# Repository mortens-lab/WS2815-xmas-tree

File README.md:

# WS2815-xmas-tree
Arduino Code and KiCad files for controller

Link to youtube video : https://youtu.be/LrLCPcfc_rA

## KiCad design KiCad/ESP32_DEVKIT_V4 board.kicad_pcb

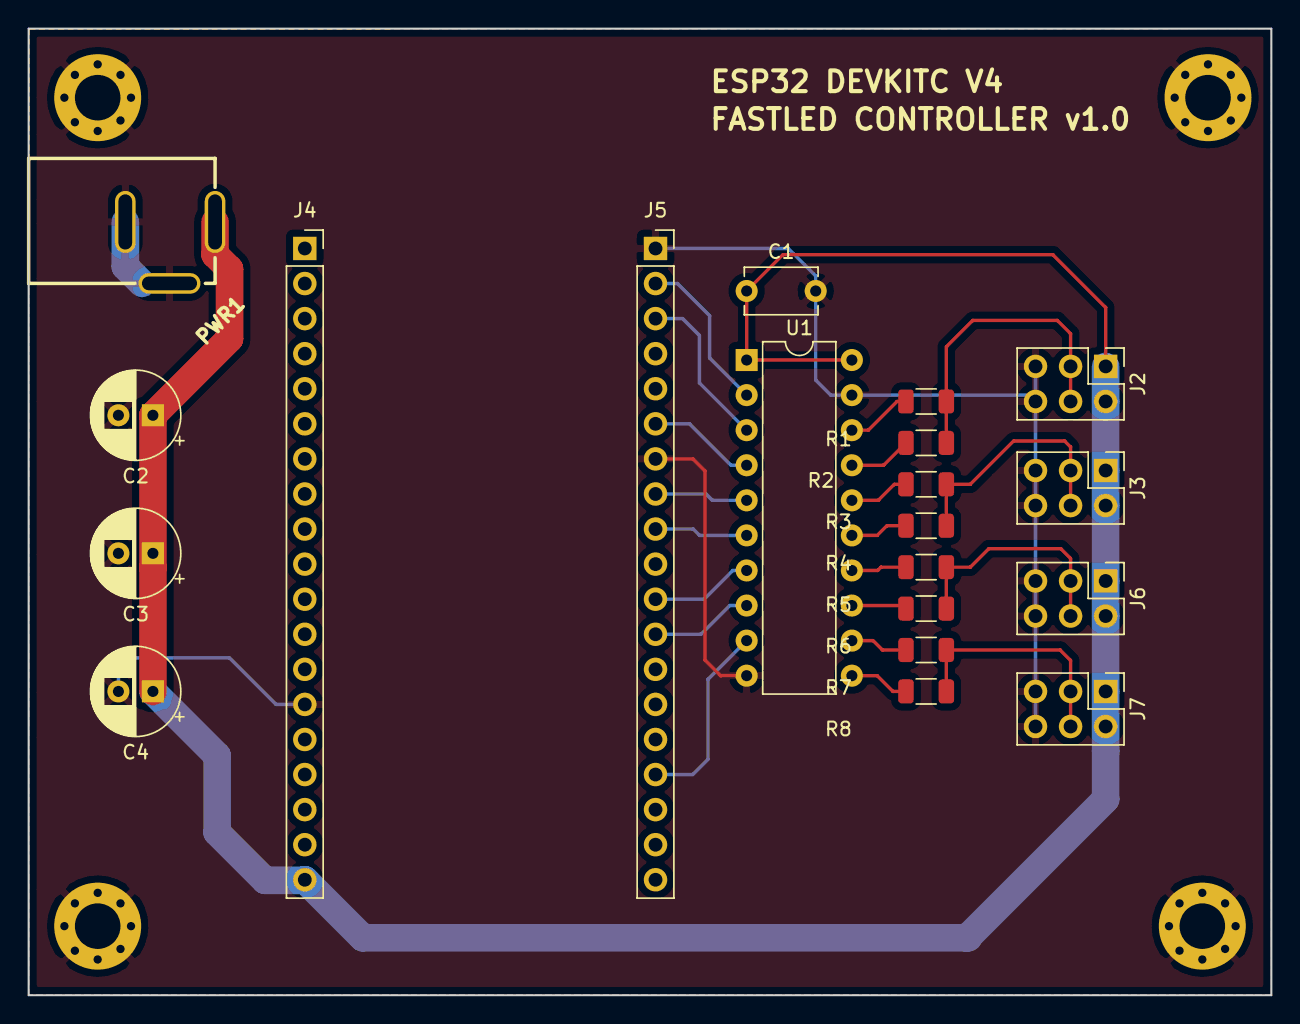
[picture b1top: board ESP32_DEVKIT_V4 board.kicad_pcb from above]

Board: 2 copper layers, 90.0 x 70.0 mm, 24 parts (0 on the bottom side), 22 nets.

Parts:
C1: 100n; C_Disc_D5.1mm_W3.2mm_P5.00mm
C2, C3, C4: 470u; CP_Radial_D6.3mm_P2.50mm
J2, J3, J6, J7: Conn_01x06; PinHeader_2x03_P2.54mm_Vertical
J4, J5: Conn_01x19; PinSocket_1x19_P2.54mm_Vertical
Mount-Hole-3.3mm1, Mount-Hole-3.3mm2, Mount-Hole-3.3mm3, Mount-Hole-3.3mm4: Mounting_hole_Shield_3.3mm
PWR1: PWR-JAKPWR_JACK_UNI_MILLING; PWRJ-2mm(YDJ-1136)
R1, R2, R3, R4, R5, R6, R7, R8: 330R; R_1206_3216Metric
U1: 74HCT245; DIP-20_W7.62mm

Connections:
/IO15: J5.16, U1.9
/IO16: J5.12, U1.8
/IO17: J5.11, U1.7
/IO18: J5.9, U1.6
/IO19: J5.8, U1.5
/IO21: J5.6, U1.4
/IO22: J5.3, U1.3
/IO23: J5.2, U1.2
GND: C1.2, C2.2, C3.2, C4.2, J2.5, J2.6, J3.5, J3.6, J4.14, J5.1, J5.7, J6.5, J6.6, J7.5, J7.6, Mount-Hole-3.3mm1.GND1, Mount-Hole-3.3mm2.GND1, Mount-Hole-3.3mm3.GND1, Mount-Hole-3.3mm4.GND1, PWR1.-, U1.10, U1.19
unnamed: J2.3, J2.4, R1.1, R2.1
unnamed: J3.3, J3.4, R3.1, R4.1
unnamed: J6.3, J6.4, R5.1, R6.1
unnamed: J7.3, J7.4, R7.1, R8.1
unnamed: R1.2, U1.18
unnamed: R2.2, U1.17
unnamed: R3.2, U1.16
unnamed: R4.2, U1.15
unnamed: R5.2, U1.14
unnamed: R6.2, U1.13
unnamed: R7.2, U1.12
unnamed: R8.2, U1.11
VCC: C1.1, C2.1, C3.1, C4.1, J2.1, J2.2, J3.1, J3.2, J4.19, J6.1, J6.2, J7.1, J7.2, PWR1.+, U1.1, U1.20

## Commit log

2024-01-09 Create LICENSE
